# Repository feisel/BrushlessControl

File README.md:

BrushlessControl
================

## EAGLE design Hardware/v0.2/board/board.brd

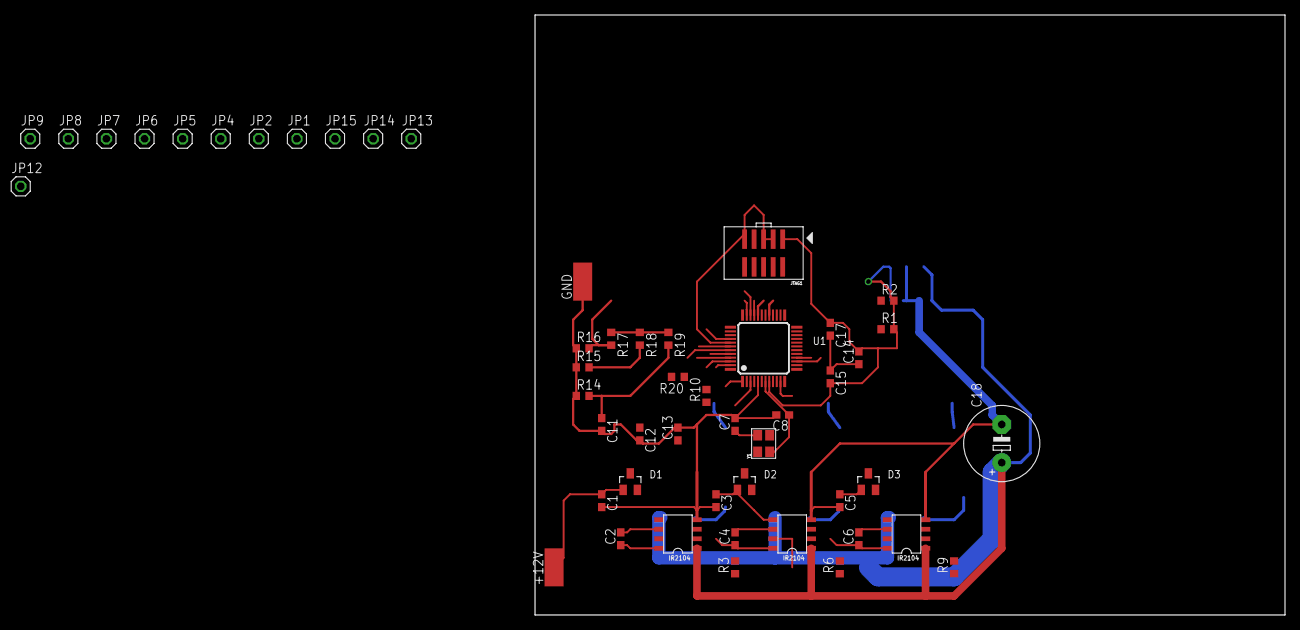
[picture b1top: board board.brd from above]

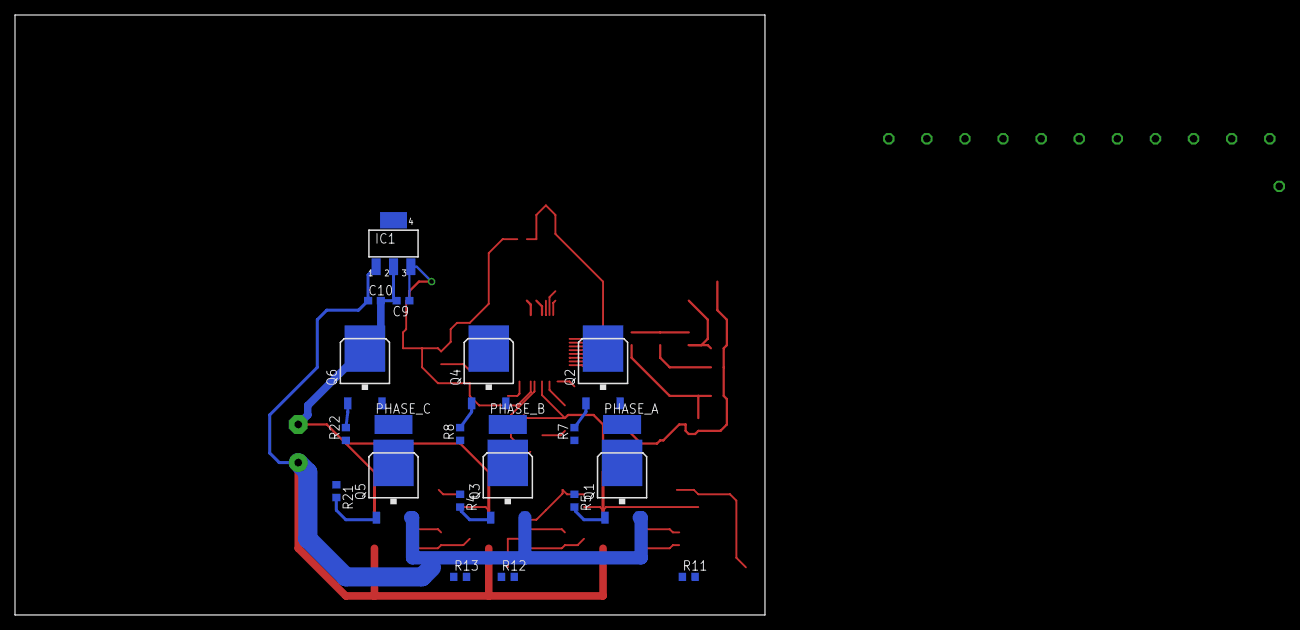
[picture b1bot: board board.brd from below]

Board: 2 copper layers, 100.0 x 80.0 mm, 72 parts (21 on the bottom side), 42 nets.

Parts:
+12V: SMD2,54-5,08
C1, C3, C5, C11, C12, C13, C14, C15: 100nF; C0603
C2, C4, C6: 220nF; C0603
C7, C8: 18pF; C0603
C9, C10, C17: 1µF; C0603
C18: 330uF; E5-10,5
D1, D2, D3: BAS21; SOT23
GND: SMD2,54-5,08
IC1: MCP1703DB; SOT223
JP1, JP2, JP4, JP5, JP6, JP7, JP8, JP9, JP12, JP13, JP14, JP15: 1X01
JTAG1: 2X05_1.27MM_SMT
PHASE_A: SMD2,54-5,08
PHASE_B: SMD2,54-5,08
PHASE_C: SMD2,54-5,08
Q1, Q2, Q3, Q4, Q5, Q6: IRLR7843; D-PAK_TO252AA
R1, R2, R3, R6, R9, R10, R20: 1k; R0603
R4, R5, R7, R8, R21, R22: 33; R0603
R11, R12, R13: 12k; R0603
R14, R15, R16, R17, R18, R19: 4k7; R0603
U1: LPC1317FBD48; SOT313-2
U$1, U$2, U$3: IR2104S
Y1: 12MHZ; CRYSTAL_3.2X2.5

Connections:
+3V3: C9.1, C14.2, C15.2, C17.1, IC1.3, JP2.1, JTAG1.1, R1.2, R2.2, R10.2, U1.8, U1.44
+12V: +12V.1, C1.1, C3.1, C5.1, C10.1, C18.+, D1.1, D2.1, D3.1, IC1.1, Q1.3, Q3.3, Q5.3, U$1.1, U$2.1, U$3.1
AVG: JP7.1, R17.1, R18.1, R19.1, R20.2
GND: C1.2, C3.2, C5.2, C7.2, C8.2, C9.2, C10.2, C11.2, C12.2, C13.2, C14.1, C15.1, C17.2, C18.-, GND.1, IC1.2, JP12.1, JTAG1.3, JTAG1.5, JTAG1.9, Q2.4, Q4.4, Q6.4, R14.1, R15.1, R16.1, U1.5, U1.41, U$1.4, U$2.4, U$3.4
IN_A: JP1.1, R3.2, U1.45, U$1.2
IN_B: JP13.1, R6.2, U1.46, U$2.2
IN_C: JP14.1, R9.2, U1.47, U$3.2
unnamed: Q1.1, R5.2
unnamed: Q2.1, R7.2
unnamed: R21.1, U$3.7
unnamed: Q5.1, R21.2
unnamed: R20.1, U1.42
unnamed: C7.1, U1.6, Y1.2
unnamed: C8.1, U1.7, Y1.1
unnamed: R4.1, U$2.7
unnamed: C2.1, D1.3, U$1.8
unnamed: Q4.1, R8.2
unnamed: R22.1, U$3.5
unnamed: Q3.1, R4.2
unnamed: R8.1, U$2.5
unnamed: R7.1, U$1.5
unnamed: R5.1, U$1.7
unnamed: C4.1, D2.3, U$2.8
unnamed: Q6.1, R22.2
unnamed: C6.1, D3.3, U$3.8
NULL_A: C13.1, JP5.1, R11.2, R16.2, R17.2, U1.33
NULL_B: C12.1, JP4.1, R12.2, R15.2, R18.2, U1.35
NULL_C: C11.1, JP6.1, R13.2, R14.2, R19.2, U1.40
PHASE_A: C2.2, PHASE_A.1, Q1.4, Q2.3, R11.1, U$1.6
PHASE_B: C4.2, PHASE_B.1, Q3.4, Q4.3, R12.1, U$2.6
PHASE_C: C6.2, PHASE_C.1, Q5.4, Q6.3, R13.1, U$3.6
PWM: JP15.1, R3.1, R6.1, R9.1, U1.43
RESET: JTAG1.10, R10.1, U1.3
SCL: JP8.1, R1.1, U1.15
SDA: JP9.1, R2.1, U1.16
SD_A: U1.21, U$1.3
SD_B: U1.1, U$2.3
SD_C: U1.11, U$3.3
SWCLK: JTAG1.4, U1.29
SWDIO: JTAG1.2, U1.39
TDI: JTAG1.8, U1.32
TDO: JTAG1.6, U1.34

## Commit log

2013-11-15 init Design
2013-11-28 Placement
2013-11-29 First routed layout
2013-12-01 optinmzed layout
2013-12-05 Included Software Baser for LPC13
2014-01-08 Removed an error on nxp.lib
2014-01-12 added two diode
2014-04-11 V2 added + stm32 Version
2014-04-11 Little Changes + GerberFiles added
